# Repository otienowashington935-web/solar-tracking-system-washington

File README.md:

# solar-tracking-system-washington

## Collaborators
1. Masika - Supervisor

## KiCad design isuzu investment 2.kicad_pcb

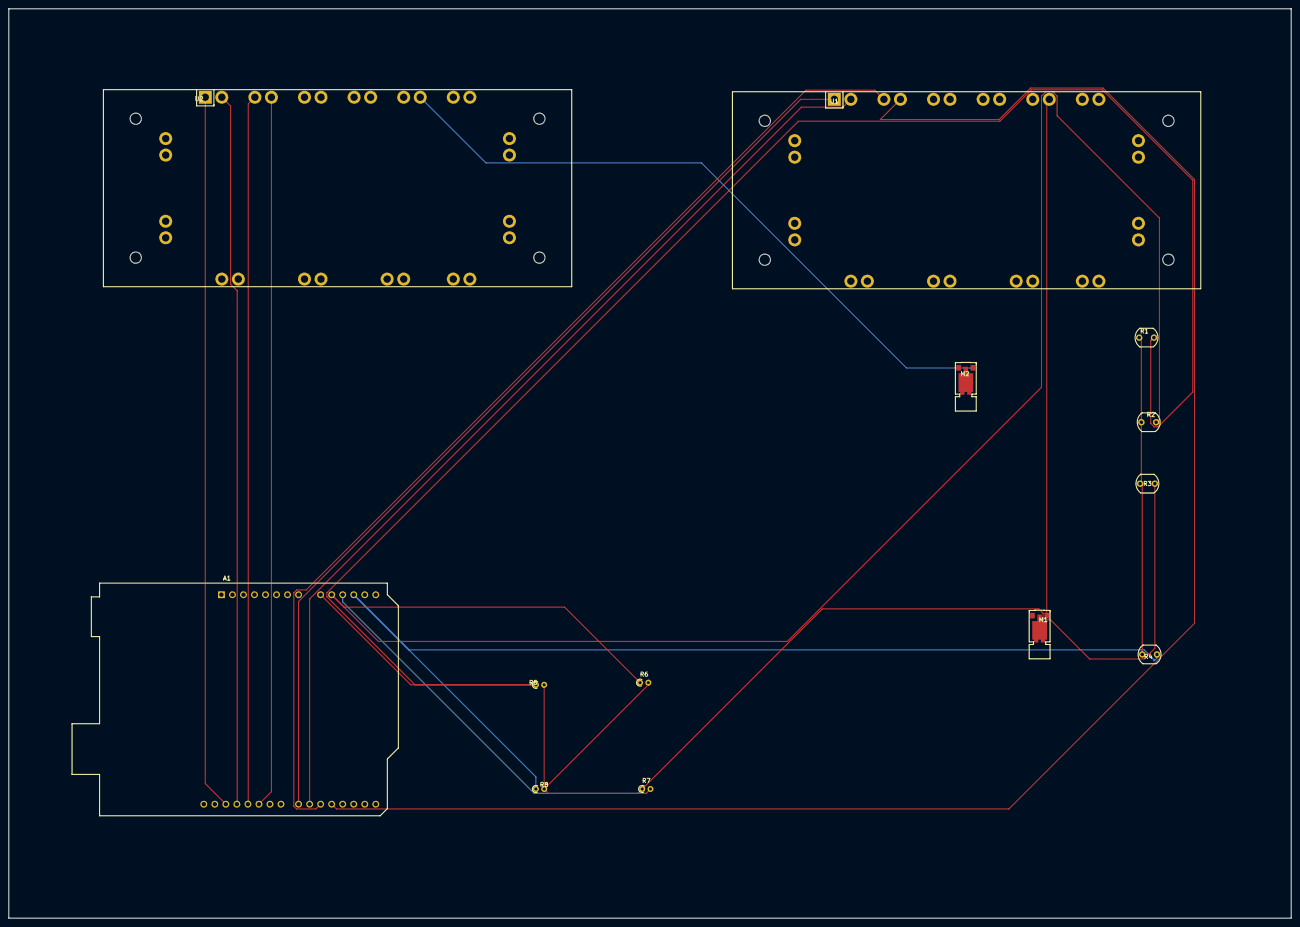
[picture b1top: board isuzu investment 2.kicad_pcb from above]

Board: 2 copper layers, 295.5 x 209.5 mm, 13 parts (0 on the bottom side), 16 nets.

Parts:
A1: Arduino_UNO_R2
M1, M2: Motor_Servo; Vybronics_VZ30C1T8219732L
R1, R2, R3, R4: LDR07; R_LDR_5.1x4.3mm_P3.4mm_Vertical
R5, R6, R7, R8: R; R_Axial_DIN0204_L3.6mm_D1.6mm_P1.90mm_Vertical
U1, U2: ULN2803A; Infineon_AG-ECONO2

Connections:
unnamed: A1.9 (A0), R1.2, R5.1
unnamed: A1.10 (A1), R2.2, R6.1
unnamed: A1.11 (A2), R3.2, R7.1
unnamed: A1.12 (A3), R4.2, R8.1
unnamed: A1.19 (D4), U1.4 (I4)
unnamed: A1.20 (D5), U1.3 (I3)
unnamed: A1.21 (D6), U1.2 (I2)
unnamed: A1.22 (D7), U1.1 (I1)
unnamed: A1.25 (D10), U2.4 (I4)
unnamed: A1.26 (D11), U2.3 (I3)
unnamed: A1.27 (D12), U2.2 (I2)
unnamed: A1.28 (D13), U2.1 (I1)
unnamed: M1.2 (+), U1.10 (COM)
unnamed: R5.2, R6.2, R7.2, R8.2
unnamed: M2.2 (+), U2.10 (COM)
unnamed: R1.1, R2.1, R3.1, R4.1
